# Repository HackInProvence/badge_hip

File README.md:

# Badge SecSea — la cigale

Le badge électronique de [SecSea](https://secsea.org/), la conférence de hacking de **Hack In Provence** à La Ciotat.
Les cigales se rencontrent par radio, échangent leurs contacts et des messages, jouent ensemble (mini-bolides,
loup-garou, tir à la corde...), chantent en chœur, affichent le programme d'une conférence, et servent d'outil
pédagogique de radio (433 MHz) et d'infrarouge.

Version : voir [VERSION](VERSION) et l'[historique des versions](CHANGELOG.md). *English: [below](#english).*

## Le matériel

| | |
|---|---|
| Microcontrôleur | RP2040 (2 cœurs à 133 MHz, 264 Ko de RAM), flash 16 Mo |
| Écran | e-Paper 1,54" 200 × 200 noir et blanc (SSD1681) |
| Radio | CC1101, 433 MHz, antenne céramique |
| Boutons | 4 : **Y A B X** de gauche à droite (A et B sur les ailes, Y et X sur les flancs) |
| Lumière, son | 2 LEDs RGB WS2812B, un buzzer |
| Stockage | carte micro-SD (images, vidéos, musique, livres-jeux, programmes de conférences...) |
| Alimentation | USB-C, batterie Li-ion avec chargeur (TP4056), régulateur 3,3 V, interrupteur |
| Extensions | 2 ports 2 × 6 : I2C, UART, SPI, infrarouge |

Le rôle de chaque composant : [l'électronique du badge](docs/fr/electronique.md). Le projet KiCad est dans
[hardware/kicad](hardware/kicad).

## Mettre en route un badge

### 1. Flasher le firmware

Le firmware est le fichier **`badge_menu.uf2`** : dans les [releases](../../releases) du dépôt, ou compilé (plus bas).

1. Interrupteur du badge sur **ON**.
2. Maintenir le bouton **BOOTSEL** (« BOOTLOAD ») du badge, brancher le câble USB, relâcher le bouton.
3. Un disque **RPI-RP2** apparaît sur l'ordinateur : copier le fichier `.uf2` dessus.
4. Le badge redémarre tout seul avec le nouveau firmware.

Avec [picotool](https://github.com/raspberrypi/picotool), sans toucher au bouton : `picotool load -f -x badge_menu.uf2`.

Au premier démarrage, le badge règle sa radio (quelques secondes), puis affiche le menu. Le numéro de version est
dans Réglages > Infos.

### 2. Préparer la carte micro-SD (facultatif)

Carte formatée en FAT32 ou exFAT. Copier à la racine le contenu de [docs/sd](docs/sd) (exemples : sonneries,
livres-jeux, programmes de conférences), puis vos images, vidéos et musiques converties (outils plus bas).

Sans sortir la carte, par l'USB : `python tools/sd_files.py` (une fenêtre : le PC à gauche, la carte à droite).

### 3. Utiliser le badge

Y / X : monter / descendre ; B : choisir ; A : retour (appui long sur A pour quitter un jeu). Tout est dans le
[guide utilisateur](docs/fr/guide_utilisateur.md).

### 4. Les outils du PC

Python 3, et selon l'outil `pip install pyserial pillow numpy` et [ffmpeg](https://ffmpeg.org/) dans le PATH.

| Outil | Usage |
|---|---|
| [tools/badge_remote.py](tools/badge_remote.py) | l'écran du badge en grand sur le PC, la télécommande, les captures (pyserial) |
| [tools/sd_files.py](tools/sd_files.py) | les fichiers de la carte SD par l'USB, dates conservées (pyserial) |
| [tools/contacts_export.py](tools/contacts_export.py) | les contacts reçus par le badge en `.vcf` (pyserial) |
| [src/images/image2epi.py](src/images/image2epi.py) | images → `.epi` pour l'écran (pillow) |
| [src/video/video2epaper.py](src/video/video2epaper.py) | vidéos → `.epv` (ffmpeg, numpy, pillow) |
| [src/audio/audio2wav.py](src/audio/audio2wav.py) | sons → `.wav` 8 bits 16 kHz (ffmpeg) |
| [tools/rtttl_sort.py](tools/rtttl_sort.py) | trier une collection de sonneries RTTTL |
| [tools/gamebook_check.py](tools/gamebook_check.py) | vérifier un livre-jeu avant de le copier |

Le site de la documentation, avec ces outils et le firmware : `python tools/docs_site.py` (dans `build/docs_site`).

## Compiler le firmware

Pré-requis : le [Pico SDK](https://www.raspberrypi.com/documentation/microcontrollers/c_sdk.html) 2.x, CMake, Ninja,
la chaîne ARM GCC, Python 3 avec Pillow. Le plus simple : l'extension VS Code **Raspberry Pi Pico**, qui installe tout
(ou le script `pico_setup.sh` de Raspberry Pi sous Debian / Ubuntu).

```bash
git clone https://github.com/HackInProvence/badge_hip.git
cd badge_hip
mkdir build && cd build
cmake .. -G Ninja -DPICO_BOARD=badge_secsea
ninja badge_menu           # → build/src/menu/badge_menu.uf2
```

Tests sur le PC : `python src/tests/host/run_tests.py` ; sur un badge branché : `python tools/badge_selftest.py`.

Tout le détail (architecture, mécanismes, formats, protocole série, tests, nouvelle version) : le
[guide développeur](docs/fr/guide_developpeur.md).

## Documentation

| | Français | English |
|---|---|---|
| Utiliser le badge | [Guide utilisateur](docs/fr/guide_utilisateur.md) | [User guide](docs/en/user_guide.md) |
| Organisateurs, carte SD, outils, flashage, dépannage | [Guide avancé](docs/fr/guide_avance.md) | [Advanced guide](docs/en/advanced_guide.md) |
| Développer | [Guide développeur](docs/fr/guide_developpeur.md) | [Developer guide](docs/en/developer_guide.md) |
| Électronique | [L'électronique du badge](docs/fr/electronique.md) | [Electronics](docs/en/electronics.md) |
| Tous les écrans | [Écrans](docs/fr/ecrans.md) | [Screens](docs/en/screens.md) |
| Badge conférence | [Badge conférence](docs/fr/badge_conference.md) | [Conference badge](docs/en/conference_badge.md) |
| Traduire | [Traduction](docs/fr/traduction.md) | [Translation](docs/en/translation.md) |

Notes de conception : [réseau, extensions et CTF](docs/idees_reseau_extensions_ctf.md),
[idées](docs/idees_brainstorm.md), [module ESP32](docs/etude_module_esp32.md) et [ses usages](docs/idees_esp32.md).

## Licence

[CC BY-NC-SA 4.0](LICENSE) — Hack In Provence.

---

## English

The electronic badge of [SecSea](https://secsea.org/), the hacking conference of Hack In Provence in La Ciotat
(France): an RP2040, a 200 × 200 e-Paper screen, a CC1101 433 MHz radio, 2 RGB LEDs, a buzzer, 4 buttons
(**Y A B X** from left to right), a micro-SD card, USB-C and a Li-ion battery.

- **Flash it**: hold **BOOTSEL**, plug the USB cable, copy `badge_menu.uf2` (from the [releases](../../releases)) to
  the **RPI-RP2** drive. Or `picotool load -f -x badge_menu.uf2`.
- **SD card** (optional): copy [docs/sd](docs/sd) to a FAT32 / exFAT card, or use `python tools/sd_files.py` over
  USB.
- **Build**: Pico SDK 2.x, then `cmake .. -G Ninja -DPICO_BOARD=badge_secsea && ninja badge_menu` in `build/`.
- **Docs**: [user guide](docs/en/user_guide.md), [advanced guide](docs/en/advanced_guide.md),
  [developer guide](docs/en/developer_guide.md), [electronics](docs/en/electronics.md),
  [changelog](CHANGELOG.md) (in French).

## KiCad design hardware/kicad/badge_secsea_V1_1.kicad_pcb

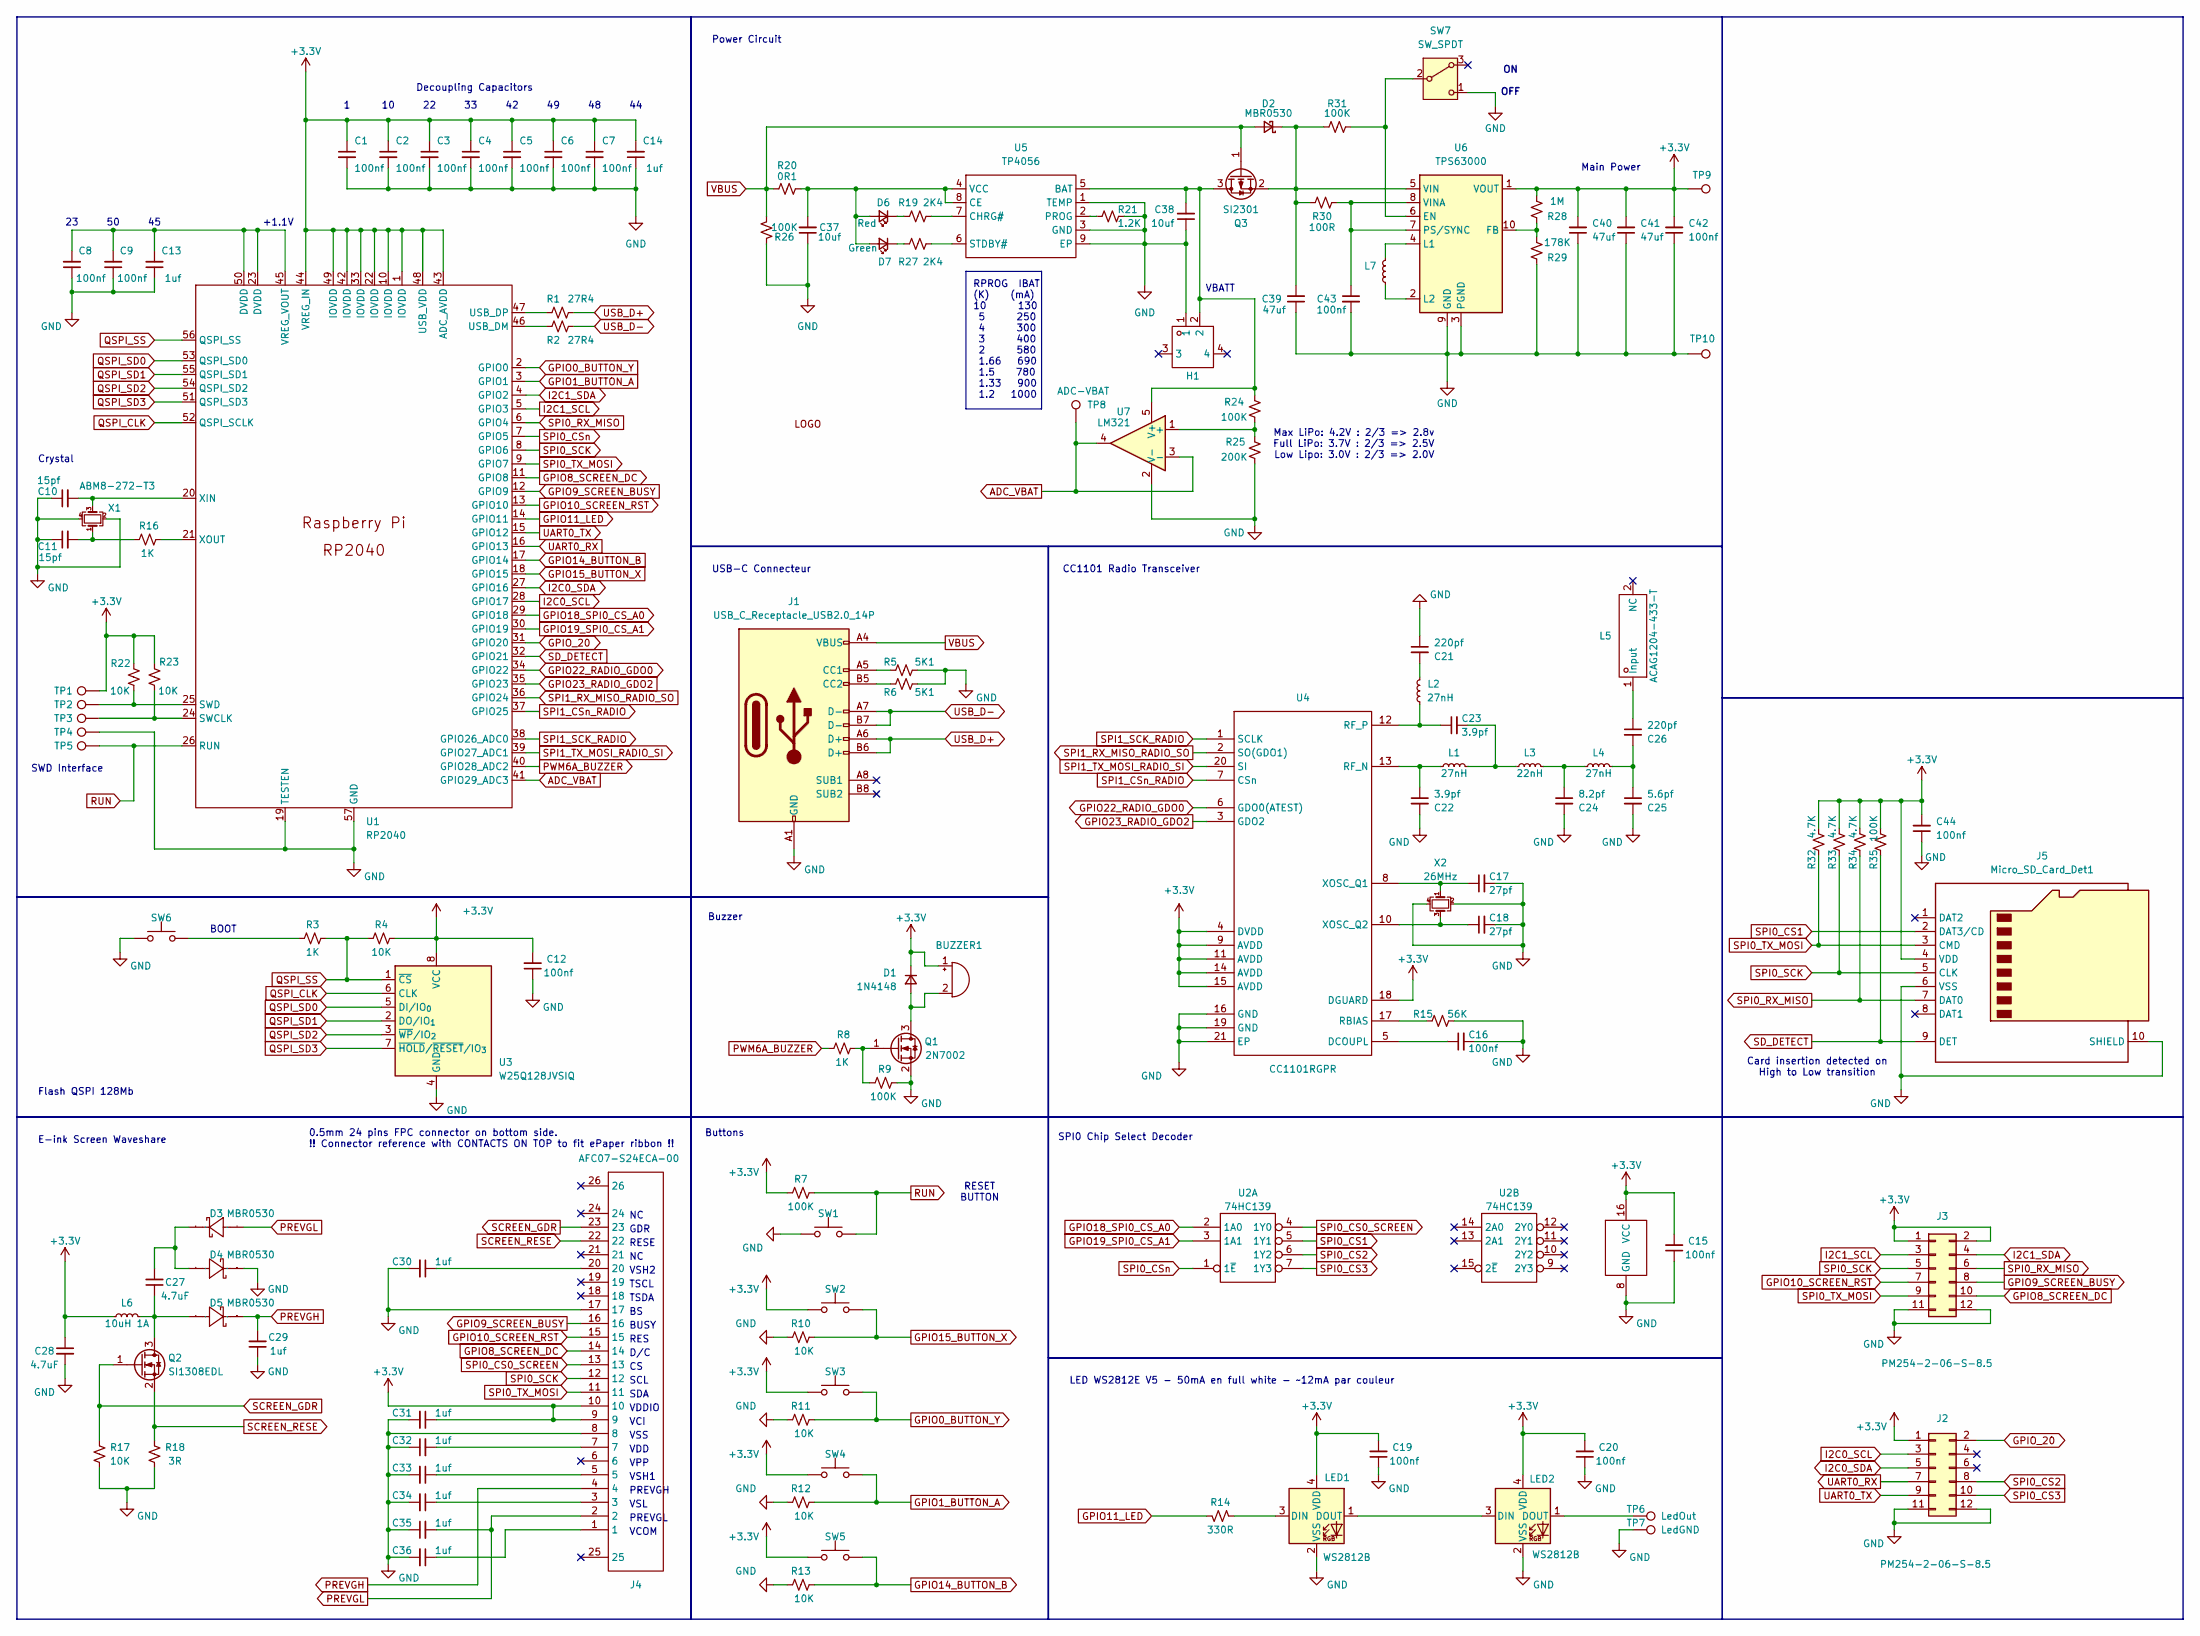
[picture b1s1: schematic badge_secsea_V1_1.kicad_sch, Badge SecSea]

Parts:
BUZZER1: MLT-8530; Buzzer MLT-8530; Manufacturer Part MLT-8530; LCSC Part # C94599
C1, C2, C3, C4, C5, C6, C7, C8, C9, C12, C15, C16, C19, C20, C42, C43, C44: 100nf; C_0402_1005Metric; Manufacturer Part CL05B104KO5NNNC; LCSC Part # C1525
C10, C11: 15pf; C_0402_1005Metric; Manufacturer Part 0402CG150J500NT; LCSC Part # C1548
C13, C14: 1uf; C_0402_1005Metric; Manufacturer Part CL05A105KA5NQNC; LCSC Part # C52923
C17, C18: 27pf; C_0402_1005Metric; Manufacturer Part 0402CG270J500NT; LCSC Part # C1557
C21, C26: 220pf; C_0402_1005Metric; Manufacturer Part 0402B221K500NT; LCSC Part # C1530
C22, C23: 3.9pf; C_0402_1005Metric; Manufacturer Part CC0402BRNPO9BN3R9; LCSC Part # C505474
C24: 8.2pf; C_0402_1005Metric; Manufacturer Part 0402CG8R2C500NT; LCSC Part # C1579
C25: 5.6pf; C_0402_1005Metric; Manufacturer Part GRM1555C1H5R6BA01D; LCSC Part # C76976
C27, C28: 4.7uF; C_0805_2012Metric; Manufacturer Part CL21A475KAQNNNE; LCSC Part # C1779
C29, C30, C31, C32, C33, C34, C35, C36: 1uf; C_0805_2012Metric; Manufacturer Part CL21B105KBFNNNE; LCSC Part # C28323
C37, C38: 10uf; C_0805_2012Metric; Manufacturer Part CL21A106KAYNNNE; LCSC Part # C15850
C39, C40, C41: 47uf; C_0805_2012Metric; Manufacturer Part CL21A476MQYNNNE; LCSC Part # C16780
D1: 1N4148; D_SOD-123; Manufacturer Part 1N4148W; LCSC Part # C81598
D2, D3, D4, D5: MBR0530; D_SOD-123; Manufacturer Part MBR0530; LCSC Part # C5204746
D6: Red; LED_0603_1608Metric; Manufacturer Part XL-1608SURC-06; LCSC Part # C965799
D7: Green; LED_0603_1608Metric; Manufacturer Part XL-1608UGC-04; LCSC Part # C965804
G1: LOGO; silkscreen_cigale
H1: WAFER-PH2.0-2PWB; CONN-SMD_2P-P2.00_XUNPU_WAFER-PH2.0-2PWB; Manufacturer Part WAFER-PH2.0-2PWB; LCSC Part # C3029440
J1: USB_C_Receptacle_USB2.0_14P; USB-C_C165948; Manufacturer Part TYPE-C-31-M-12; LCSC Part # C165948
J2, J3: PM254-2-06-S-8.5; PinSocket_2x06_P2.54mm_Vertical_SMD; Manufacturer Part PM254-2-06-S-8.5; LCSC Part # C3975151
J4: AFC07-S24ECA-00; FPC_24; Manufacturer Part AFC07-S24ECA-00; LCSC Part # C262643
J5: Micro_SD_Card_Det1; MicroSD TF-115-BCP9; Manufacturer Part XUNPU TF-115-BCP9; LCSC Part # C720505
L1, L2, L4: 27nH; L_0402_1005Metric; Manufacturer Part LQG15HS27NJ02D; LCSC Part # C12669
L3: 22nH; L_0402_1005Metric; Manufacturer Part SDCL1005C22NJTDF; LCSC Part # C15178
L5: ACAG1204-433-T; ANT-SMD_L12.0-W4.0_ACAG1204-915-T; Manufacturer Part ACAG1204-433-T; LCSC Part # C6113830
L6: 10uH 1A; L_Ferrocore_DLG-0403; Manufacturer Part CY43-10UH; LCSC Part # C2929419
L7: 2.2µH; L_APV_ANR4012; Manufacturer Part NR4018S2R2MT; LCSC Part # C28642347
LED1, LED2: WS2812B; LED_WS2812B-2020_PLCC4_2.0x2.0mm; Manufacturer Part WS2812B-2020; LCSC Part # C965555
Q1: 2N7002; SOT-23; Manufacturer Part 2N7002; LCSC Part # C8545
Q2: SI1308EDL; SOT-323_SC-70; Manufacturer Part SI1308EDL; LCSC Part # C7603347
Q3: SI2301; SOT-23; Manufacturer Part SI2301; LCSC Part # C2891731
R1, R2: 27R4; R_0402_1005Metric; Manufacturer Part RC-02W27R4FT; LCSC Part # C321420
R3, R8, R16: 1K; R_0402_1005Metric; Manufacturer Part 0402WGF1001TCE; LCSC Part # C11702
R4, R10, R11, R12, R13, R17, R22, R23: 10K; R_0402_1005Metric; Manufacturer Part 0402WGF1002TCE; LCSC Part # C25744
R5, R6: 5K1; R_0402_1005Metric; Manufacturer Part 0402WGF5101TCE; LCSC Part # C25905
R7, R9, R24, R26, R31, R35: 100K; R_0402_1005Metric; Manufacturer Part 0402WGF1003TCE; LCSC Part # C25741
R14: 330R; R_0402_1005Metric; Manufacturer Part 0402WGF3300TCE; LCSC Part # C25104
R15: 56K; R_0402_1005Metric; Manufacturer Part 0402WGF5602TCE; LCSC Part # C25796
R18: 3R; R_0402_1005Metric; Manufacturer Part FRC0402F3R00TS; LCSC Part # C2933093
R19, R27: 2K4; R_0402_1005Metric; Manufacturer Part 0402WGF2401TCE; LCSC Part # C25882
R20: 0R1; R_1206_3216Metric; Manufacturer Part 1206W4F100LT5E; LCSC Part # C25334
R21: 1.2K; R_0805_2012Metric_Pad1.20x1.40mm_HandSolder; Manufacturer Part 0805W8F1201T5E; LCSC Part # C17379
R25: 200K; R_0402_1005Metric; Manufacturer Part 0402WGF2003TCE; LCSC Part # C25764
R28: 1M; R_0402_1005Metric; Manufacturer Part FRC0402F1004TS; LCSC Part # C2909328
R29: 178K; R_0402_1005Metric; Manufacturer Part FRC0402F1783TS; LCSC Part # C3013156
R30: 100R; R_0402_1005Metric; Manufacturer Part FRC0402J101TS; LCSC Part # C2906884
R32, R33, R34: 4.7K; R_0402_1005Metric; Manufacturer Part FRC0402J472 TS; LCSC Part # C2906941
SW1, SW6: TS-1187A-B-A-B; SW_Push_1P1T_XKB_TS-1187A; Manufacturer Part TS-1187A-B-A-B; LCSC Part # C318884
SW2, SW3: K2-1112SW-A4SW-04; Manufacturer Part K2-1112SW-A4SW-04; LCSC Part # C223811
SW4, SW5: XDTD-6650; SW_Push_1P1T_NO_E-Switch_TL3301NxxxxxG; Manufacturer Part XDTD-6643-L01; LCSC Part # C7498208
SW7: SW_SPDT; SPDT SMD slide switch; Manufacturer Part SSSS811101; LCSC Part # C109335
TP1, TP2, TP3, TP4, TP5: TestPoint; TestPoint_Pad_D1.5mm
TP6: LedOut; TestPoint_Pad_D1.5mm
TP7: LedGND; TestPoint_Pad_D1.5mm
TP8, TP9, TP10: ADC-VBAT; TestPoint_Pad_D1.5mm
U1: RP2040; QFN-56-1EP_7x7mm_P0.4mm_EP3.2x3.2mm; Manufacturer Part RP2040; LCSC Part # C2040
U2: 74HC139; SOIC-16_3.9x9.9mm_P1.27mm; Manufacturer Part 74HC139D,653; LCSC Part # C5603
U3: W25Q128JVSIQ; SOIC-8_5.3x5.3mm_P1.27mm; Manufacturer Part W25Q128JVSIQ; LCSC Part # C97521
U4: CC1101RGPR; QFN-20-1EP_L4.0-W4.0-P0.5-EP2.4; Manufacturer Part CC1101RGPR; LCSC Part # C29953
U5: TP4056; ESOP-8_L4.9-W3.9-P1.27-LS6.0-BL-EP; Manufacturer Part TP4056; LCSC Part # C725790
U6: TPS63000; Texas_DRC0010J; Manufacturer Part TPS63000DRCR; LCSC Part # C24966
U7: LM321; SOT-23-5; Manufacturer Part LM321H-TR; LCSC Part # C2927688
X1: ABM8-272-T3; Crystal_SMD_Abracon_ABM8AIG-4Pin_3.2x2.5mm; Manufacturer Part ABM8-272-T3; LCSC Part # C20625731
X2: 26MHz; Crystal_SMD_3225-4Pin_3.2x2.5mm; Manufacturer Part S3226000151040; LCSC Part # C479205

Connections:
+3.3V: BUZZER1.1 (+), C1.1, C2.1, C3.1, C4.1, C5.1, C6.1, C7.1, C12.2, C14.2, C15.2, C19.2, C20.2, C28.1, C31.1, C40.2, C41.2, C42.2, C44.2, D1.1 (K), J2.1, J3.1, J3.2, J4.9, J4.10, J5.4 (VDD), L6.1, LED1.4 (VDD), LED2.4 (VDD), R4.2, R7.1, R22.2, R23.2, R28.1, R32.2, R33.2, R34.2, R35.2, SW2.1, SW3.2, SW4.2, SW5.2, TP1.1, TP9.1, U1.1 (IOVDD), U1.10 (IOVDD), U1.22 (IOVDD), U1.33 (IOVDD), U1.42 (IOVDD), U1.43 (ADC_AVDD), U1.44 (VREG_IN), U1.48 (USB_VDD), U1.49 (IOVDD), U2.16 (VCC), U3.8 (VCC), U4.4 (DVDD), U4.9 (AVDD), U4.11 (AVDD), U4.14 (AVDD), U4.15 (AVDD), U4.18 (DGUARD), U6.1 (VOUT)
ADC_VBAT: TP8.1, U1.41 (GPIO29_ADC3), U7.3 (-), U7.4
GND: C1.2, C2.2, C3.2, C4.2, C5.2, C6.2, C7.2, C8.1, C9.1, C10.1, C11.1, C12.1, C13.1, C14.1, C15.1, C16.2, C17.2, C18.2, C19.1, C20.1, C21.1, C22.2, C24.2, C25.2, C28.2, C29.1, C30.2, C31.2, C32.1, C33.2, C34.2, C35.1, C36.2, C37.1, C38.1, C39.1, C40.1, C41.1, C42.1, C43.2, C44.1, D4.1 (K), H1.1, J1.A1 (GND), J1.B1 (GND), J2.11, J2.12, J3.11, J3.12, J4.8, J4.17, J5.6 (VSS), J5.10 (SHIELD), LED1.2 (VSS), LED2.2 (VSS), Q1.2 (S), R5.1, R6.2, R9.2, R10.1, R11.1, R12.1, R13.1, R15.2, R17.1, R18.1, R21.1, R25.1, R26.2, R29.2, SW1.1, SW6.1, SW7.1 (C), TP4.1, TP7.1, TP10.1, U1.19 (TESTEN), U1.57 (GND), U2.8 (GND), U3.4 (GND), U4.16 (GND), U4.19 (GND), U4.21 (EP), U5.1 (TEMP), U5.3 (GND), U5.9 (EP), U6.3 (PGND), U6.9 (GND), U6.11 (PGND), U7.2 (V-), X1.2, X1.4, X2.2, X2.4
GPIO0_BUTTON_Y: R11.2, SW3.1, U1.2 (GPIO0)
GPIO1_BUTTON_A: R12.2, SW4.1, U1.3 (GPIO1)
GPIO8_SCREEN_DC: J3.10, J4.14, U1.11 (GPIO8)
GPIO9_SCREEN_BUSY: J3.8, J4.16, U1.12 (GPIO9)
GPIO10_SCREEN_RST: J3.7, J4.15, U1.13 (GPIO10)
GPIO11_LED: R14.1, U1.14 (GPIO11)
GPIO14_BUTTON_B: R13.2, SW5.1, U1.17 (GPIO14)
GPIO15_BUTTON_X: R10.2, SW2.2, U1.18 (GPIO15)
GPIO18_SPI0_CS_A0: U1.29 (GPIO18), U2.2 (1A0)
GPIO19_SPI0_CS_A1: U1.30 (GPIO19), U2.3 (1A1)
GPIO22_RADIO_GDO0: U1.34 (GPIO22), U4.6 (GDO0(ATEST))
GPIO23_RADIO_GDO2: U1.35 (GPIO23), U4.3 (GDO2)
GPIO_20: J2.2, U1.31 (GPIO20)
I2C0_SCL: J2.3, U1.28 (GPIO17)
I2C0_SDA: J2.5, U1.27 (GPIO16)
I2C1_SCL: J3.3, U1.5 (GPIO3)
I2C1_SDA: J3.4, U1.4 (GPIO2)
unnamed: BUZZER1.2 (-), D1.2 (A), Q1.3 (D)
unnamed: C11.2, R16.1, X1.1
unnamed: C21.2, L2.2
unnamed: C23.2, L1.2, L3.1
unnamed: C24.1, L3.2, L4.1
unnamed: C25.1, C26.2, L4.2
unnamed: C30.1, J4.20
unnamed: C32.2, J4.7
unnamed: C33.1, J4.5
unnamed: C34.1, J4.3
unnamed: C36.1, J4.1
unnamed: C39.2, D2.1 (K), Q3.2 (S), R30.2, R31.1, U6.5 (VIN)
unnamed: C27.2, D3.1 (K), D4.2 (A)
unnamed: C27.1, D5.2 (A), L6.2, Q2.3 (D)
unnamed: C37.2, D6.2 (A), D7.2 (A), R20.1, U5.4 (VCC), U5.8 (CE)
unnamed: D6.1 (K), R19.2
unnamed: D7.1 (K), R27.2
unnamed: J1.A5 (CC1), R5.2
unnamed: J1.B5 (CC2), R6.1
unnamed: C26.1, L5.1 (Input)
unnamed: LED1.3 (DIN), R14.2
unnamed: LED1.1 (DOUT), LED2.3 (DIN)
unnamed: LED2.1 (DOUT), TP6.1
unnamed: Q1.1 (G), R8.2, R9.1
unnamed: C38.2, H1.2, Q3.3 (D), R24.2, U5.5 (BAT), U7.5 (V+)
unnamed: R3.2, SW6.2
unnamed: R31.2, SW7.2 (B), U6.6 (EN)
unnamed: R23.1, TP3.1, U1.24 (SWCLK)
unnamed: R22.1, TP2.1, U1.25 (SWD)
unnamed: R2.1, U1.46 (USB_DM)
unnamed: R1.2, U1.47 (USB_DP)
unnamed: C8.2, C9.2, C13.2, U1.23 (DVDD), U1.45 (VREG_VOUT), U1.50 (DVDD)
unnamed: C10.2, U1.20 (XIN), X1.3
unnamed: R16.2, U1.21 (XOUT)
unnamed: C16.1, U4.5 (DCOUPL)
unnamed: R15.1, U4.17 (RBIAS)
unnamed: C22.1, L1.1, U4.13 (RF_N)
unnamed: C23.1, L2.1, U4.12 (RF_P)
unnamed: C17.1, U4.8 (XOSC_Q1), X2.1
unnamed: C18.1, U4.10 (XOSC_Q2), X2.3
unnamed: R19.1, U5.7 (CHRG#)
unnamed: R21.2, U5.2 (PROG)
unnamed: R27.1, U5.6 (STDBY#)
unnamed: R28.2, R29.1, U6.10 (FB)
unnamed: L7.2, U6.4 (L1)
unnamed: L7.1, U6.2 (L2)
unnamed: C43.1, R30.1, U6.7 (PS/SYNC), U6.8 (VINA)
unnamed: R24.1, R25.2, U7.1 (+)
PREVGH: C29.2, D5.1 (K), J4.4
PREVGL: C35.2, D3.2 (A), J4.2
PWM6A_BUZZER: R8.1, U1.40 (GPIO28_ADC2)
QSPI_CLK: U1.52 (QSPI_SCLK), U3.6 (CLK)
QSPI_SD0: U1.53 (QSPI_SD0), U3.5 (DI/IO_{0})
QSPI_SD1: U1.55 (QSPI_SD1), U3.2 (DO/IO_{1})
QSPI_SD2: U1.54 (QSPI_SD2), U3.3 (~WP/IO_{2})
QSPI_SD3: U1.51 (QSPI_SD3), U3.7 (~HOLD/~RESET/IO_{3})
QSPI_SS: R3.1, R4.1, U1.56 (QSPI_SS), U3.1 (~CS)
RUN: R7.2, SW1.2, TP5.1, U1.26 (RUN)
SCREEN_GDR: J4.23, Q2.1 (G), R17.2
SCREEN_RESE: J4.22, Q2.2 (S), R18.2
SD_DETECT: J5.9 (DET), R35.1, U1.32 (GPIO21)
SPI0_CS0_SCREEN: J4.13, U2.4 (1Y0)
SPI0_CS1: J5.2 (DAT3/CD), U2.5 (1Y1)
SPI0_CS2: J2.8, U2.6 (1Y2)
SPI0_CS3: J2.10, U2.7 (1Y3)
SPI0_CSn: U1.7 (GPIO5), U2.1 (1~E)
SPI0_RX_MISO: J3.6, J5.7 (DAT0), R34.1, U1.6 (GPIO4)
SPI0_SCK: J3.5, J4.12, J5.5 (CLK), R33.1, U1.8 (GPIO6)
SPI0_TX_MOSI: J3.9, J4.11, J5.3 (CMD), R32.1, U1.9 (GPIO7)
SPI1_CSn_RADIO: U1.37 (GPIO25), U4.7 (CSn)
SPI1_RX_MISO_RADIO_SO: U1.36 (GPIO24), U4.2 (SO(GDO1))
SPI1_SCK_RADIO: U1.38 (GPIO26_ADC0), U4.1 (SCLK)
SPI1_TX_MOSI_RADIO_SI: U1.39 (GPIO27_ADC1), U4.20 (SI)
UART0_RX: J2.7, U1.16 (GPIO13)
UART0_TX: J2.9, U1.15 (GPIO12)
USB_D+: J1.A6 (D+), J1.B6 (D+), R1.1
USB_D-: J1.A7 (D-), J1.B7 (D-), R2.2
VBUS: D2.2 (A), J1.A4 (VBUS), J1.B4 (VBUS), Q3.1 (G), R20.2, R26.1

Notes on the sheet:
VDD
VDDIO
E-ink Screen Waveshare
Main Power
RPROG IBAT (K) (mA) 10 130 5 250 4 300 3 400 2 580 1.66 690 1.5 780 1.33 900 1.2 1000
VSH1
VPP
TSCL
Flash QSPI 128Mb
VCOM
PREVGH
SDA
VSH2
Max LiPo: 4.2V : 2/3 => 2.8v Full LiPo: 3.7V : 2/3 => 2.5V Low Lipo: 3.0V : 2/3 => 2.0V
Buzzer
ON OFF
+1.1V
RES
GDR
Buttons
D/C
CC1101 Radio Transceiver
Card insertion detected on High to Low transition
VCI
BUSY
Crystal
Decoupling Capacitors
PREVGL
SPI0 Chip Select Decoder
LED WS2812E V5 - 50mA en full white - ~12mA par couleur
VSS
VSL
SCL
RESET BUTTON
VBATT
SWD Interface
Power Circuit
RESE
TSDA
USB-C Connecteur

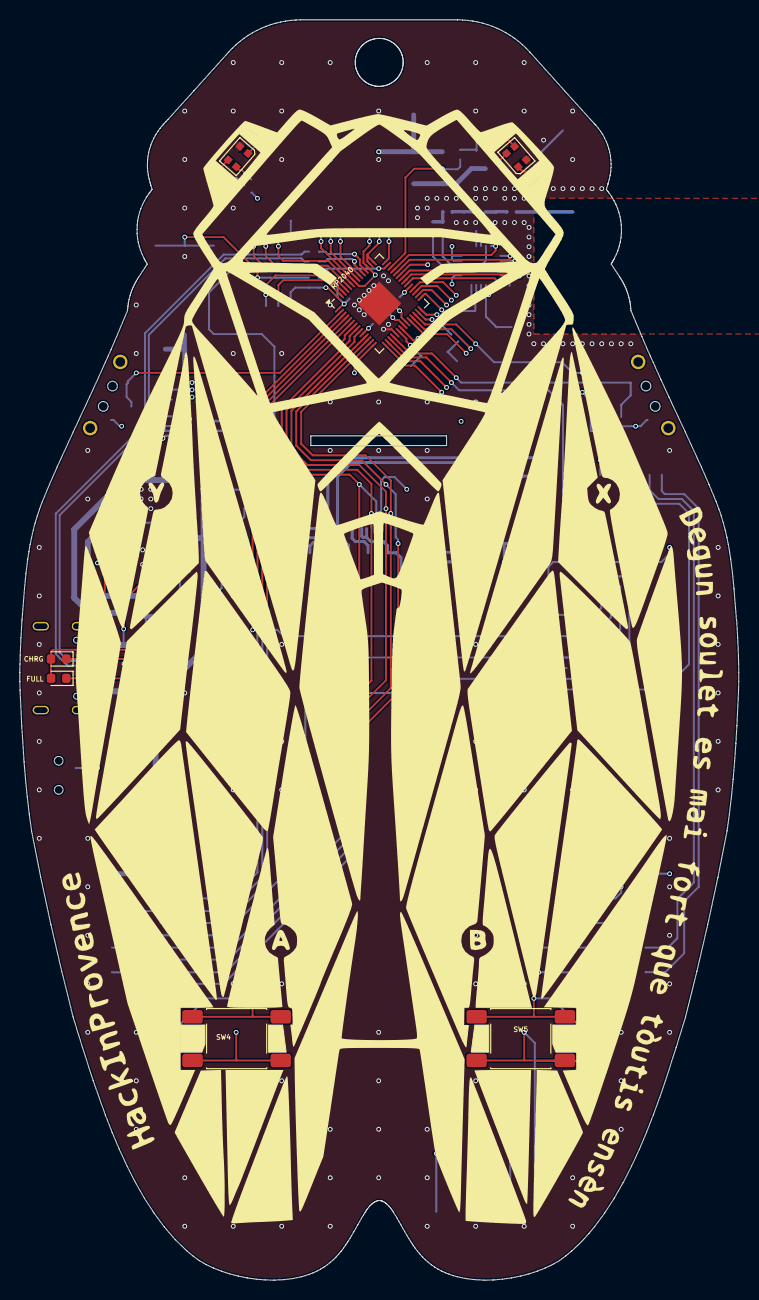
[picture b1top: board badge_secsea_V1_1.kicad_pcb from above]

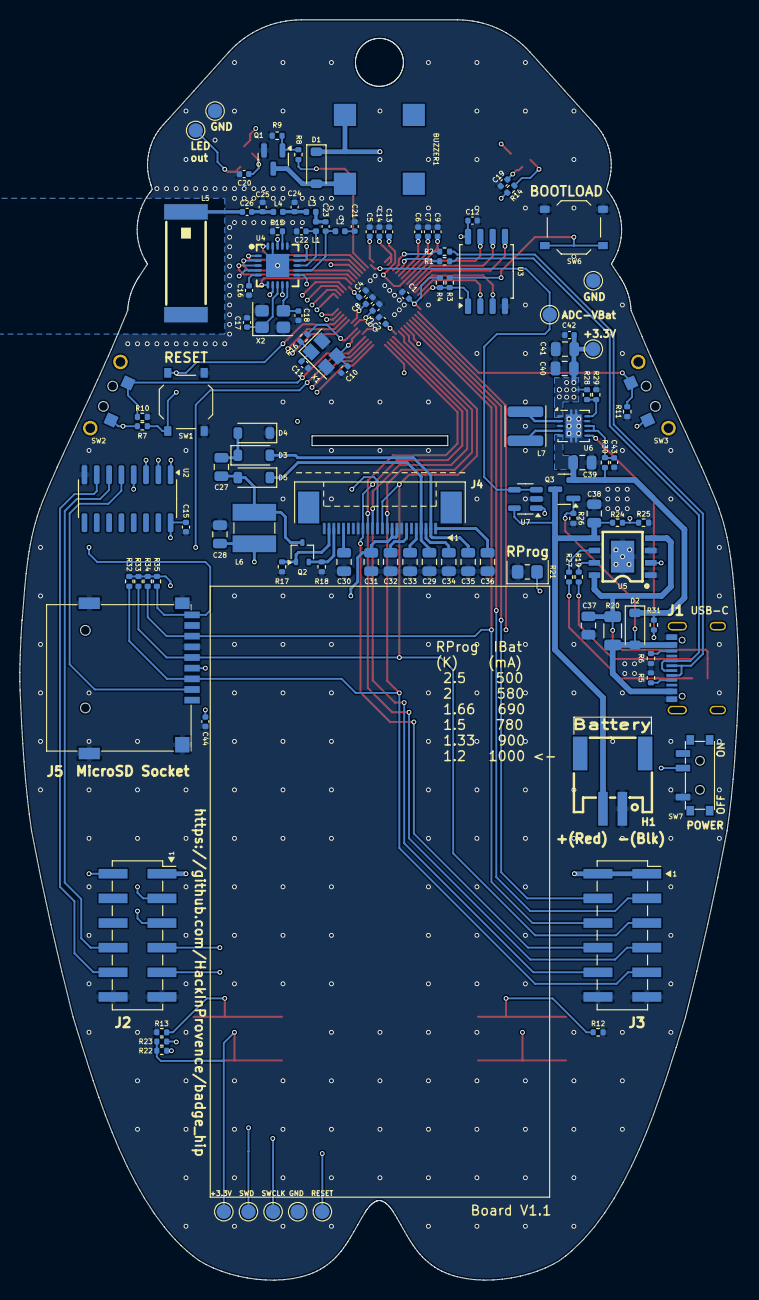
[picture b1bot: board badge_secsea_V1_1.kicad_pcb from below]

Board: 4 copper layers, 74.1 x 130.0 mm, 132 parts (124 on the bottom side), 98 nets.

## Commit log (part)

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2025-10-03 Cicada sound prototype
2025-10-03 Cicada: better timings
2025-10-03 Cicada: fix silences
2025-10-04 Cicada: notes are 4+4 bits now
2025-10-06 Cicada: use interrupts to fill the fifo
2025-10-06 Cicada: refactor the code to have a library
2025-10-07 Cicada: refactor the code to make the cmake library
2025-10-07 Add the CC-BY-NC-SA 4.0 license to our work
2025-10-07 Add templates for new libraries
2025-10-08 Cicada: adapt to new definitions of badge pinout
2025-10-08 Music: add a melody player using the PWM
2025-10-08 Instructions for VSCode
2025-10-08 Build configuration for the badge_secsea
2025-10-09 Hardware: add hardware electric design
2025-10-09 Workshop: overview and activities
2025-10-09 Music: fix beat + set_enabled
2025-10-09 Workshop: more activities
2025-10-10 Workshop: Adjust demo commands
2025-10-10 Workshop: Readjust demo commands
2025-10-11 Cicada: there's a bug
2025-10-17 ePaper: dirty hacks to enable 4 shades of gray
2025-10-18 ePaper: correct pinout
2025-10-19 ePaper: move most of the code from test to library
2025-10-19 ePaper: fix screen_busy
2025-10-19 ePaper: rewrite the API, hopefully more useable
2025-10-22 ePaper: accept partial images
2025-10-23 CC1101: handle asynch mode TX
2025-10-23 Add binary declarations to music and noise_gen libs
2025-10-23 CC1101: handle asynch mode RX and TX
2025-10-23 CC1101: refactor asynch mode tests
2025-10-24 CC1101: talk to Flipper's enhanced SubGHz chat app
2025-10-24 CC1101: move radio_boot
2025-10-24 CC1101: try to calibrate my module's crystal -> need multicore
2025-10-27 CC1101: calibrate with multicore
2025-10-27 LEDs: test program for the LEDs
2025-10-28 Btns: skeleton library
2025-10-28 Create a badge and badge_images cmake libraries to simplify includes and image2epaper transformations
2025-10-28 Use badge in all library projects
2025-10-28 Logs: add a log library that can be disabled at compile time or at runtime
2025-10-28 Add a STATIC definition that is bypassed in tests so that static are testable
2025-10-29 Fix STATIC definition
2025-10-29 ePaper: introduce animations
2025-10-29 ePaper: add logs to the library and prepare for more features
2025-10-31 ePaper: test different animation settings
2025-10-31 ePaper: test with A0 and A1 low
2025-11-01 ePaper: 13fps test
2025-11-01 ePaper: replace all calls to send by calls using the send macro
2025-11-03 ePaper: need an animation testbench
2025-11-03 ePaper: move the multiframe API from tests to library
2025-11-03 ePaper: draft for test bench to improve colors
2025-11-04 ePaper: make better transitions wave settings with better testbench
2025-11-05 Move badge_pinout.h to pinouts.h to prepare for variants of the badge
2025-11-05 Define 2 new boards: my proto (badge_proto) and a radio emitter (pico+CC1101)
2025-11-05 CC1101: make the library configurable from the PICO_BOARD header and cmake command line
2025-11-06 RaSo: start the radio source UART bridge
2025-11-06 LEDs: color animation library using timers
2025-11-06 RaSo: hex echoer
2025-11-06 RaSo: put a python script to send data to the RaSo
2025-11-06 RaSo: test UART over USB filled up
2025-11-06 CC1101: move functions from test to API
2025-11-07 RaSo: serial to air bridge working
2025-11-17 RaSo: receive what we send + add radio_set_baud_rate
2025-11-17 RaSo: try to receive without SYNC word, not very successful
2025-11-17 RaSo: confirm how CS works
2025-11-24 RaSo: laboriously receive packets of unknown lengths
2025-11-27 RaSo: raw FSK fixed length, but limited to 64 bytes
2025-11-28 RaSo: "infinite" length mode to send bigger packets
2025-11-28 CC1101: in fact, you can't burst read status registers, it's written in the datasheet
2025-12-01 CC1101: parse UART
2025-12-02 RaSo: refactor to ease reception
2025-12-02 CC1101: fix radio_wait_state dead locking without warning
2025-12-02 RaSo: merge infinite and fixed length modes
2025-12-02 RaSo: move RX from tests to RaSo
2025-12-03 RaSo: fix LED color for RSSI
2025-12-03 RaSo: rewrite state machines to handle RX+TX
2025-12-18 RaSo: changed the condition to go from INFINITE to FIXED packet length mode
2025-12-18 RaSo: fix infinite length mode not handling correctly small packets
2025-12-18 RaSo: moved variable length logic to C
2025-12-18 RaSo: fix TX underflowing on variable length packets
2026-06-19 ePaper: re-testing animations
2026-06-19 CC1101: calibration info et re-test with the flipper
2026-06-19 RaSo: trying to fix some forgotten bug
2026-06-19 ePaper: use hip 4 grays in tests
2026-06-19 Update instructions after last years's workshop...
2026-06-19 Add the hardware sources, current version + schematics for the produced version
